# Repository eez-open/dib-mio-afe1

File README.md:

The [EEZ DIB](https://github.com/eez-open/modular-psu) 4-channel Hi-voltage/Hi-current AFE for [MIO168](https://github.com/eez-open/dib-mio168) module.

### Feature list
* [ADS131E04](https://www.ti.com/product/ADS131E04) 24-bit 4-channel simultaneous sampling ADC with SPI
* 5½ digit effective resolution
* 2 x Hi-voltage channels featuring software selectable 3 measurement ranges (±2.4 V, ±12 V, ±240 V), and one current range (±240 mA)
* 2 x Hi-current channels featuring software selectable 3 measurement ranes (±24 mA, ±1 A, ±10 A) and 2 voltage ranges (±2.4 V, ±12 V)
* Latching relays for lower continous power consumption
* On-board ±2.5 V low noise LDOs
* Optional Voltage reference (LTC6655-2.5)
* Active clamps on ADC inputs
* 20 x 5 mm fueses on hi-current channels (AIN3 and AIN4)
* Dimensions: 143 x 68.5 mm, 4-layer PCB

### r1B2 prototype

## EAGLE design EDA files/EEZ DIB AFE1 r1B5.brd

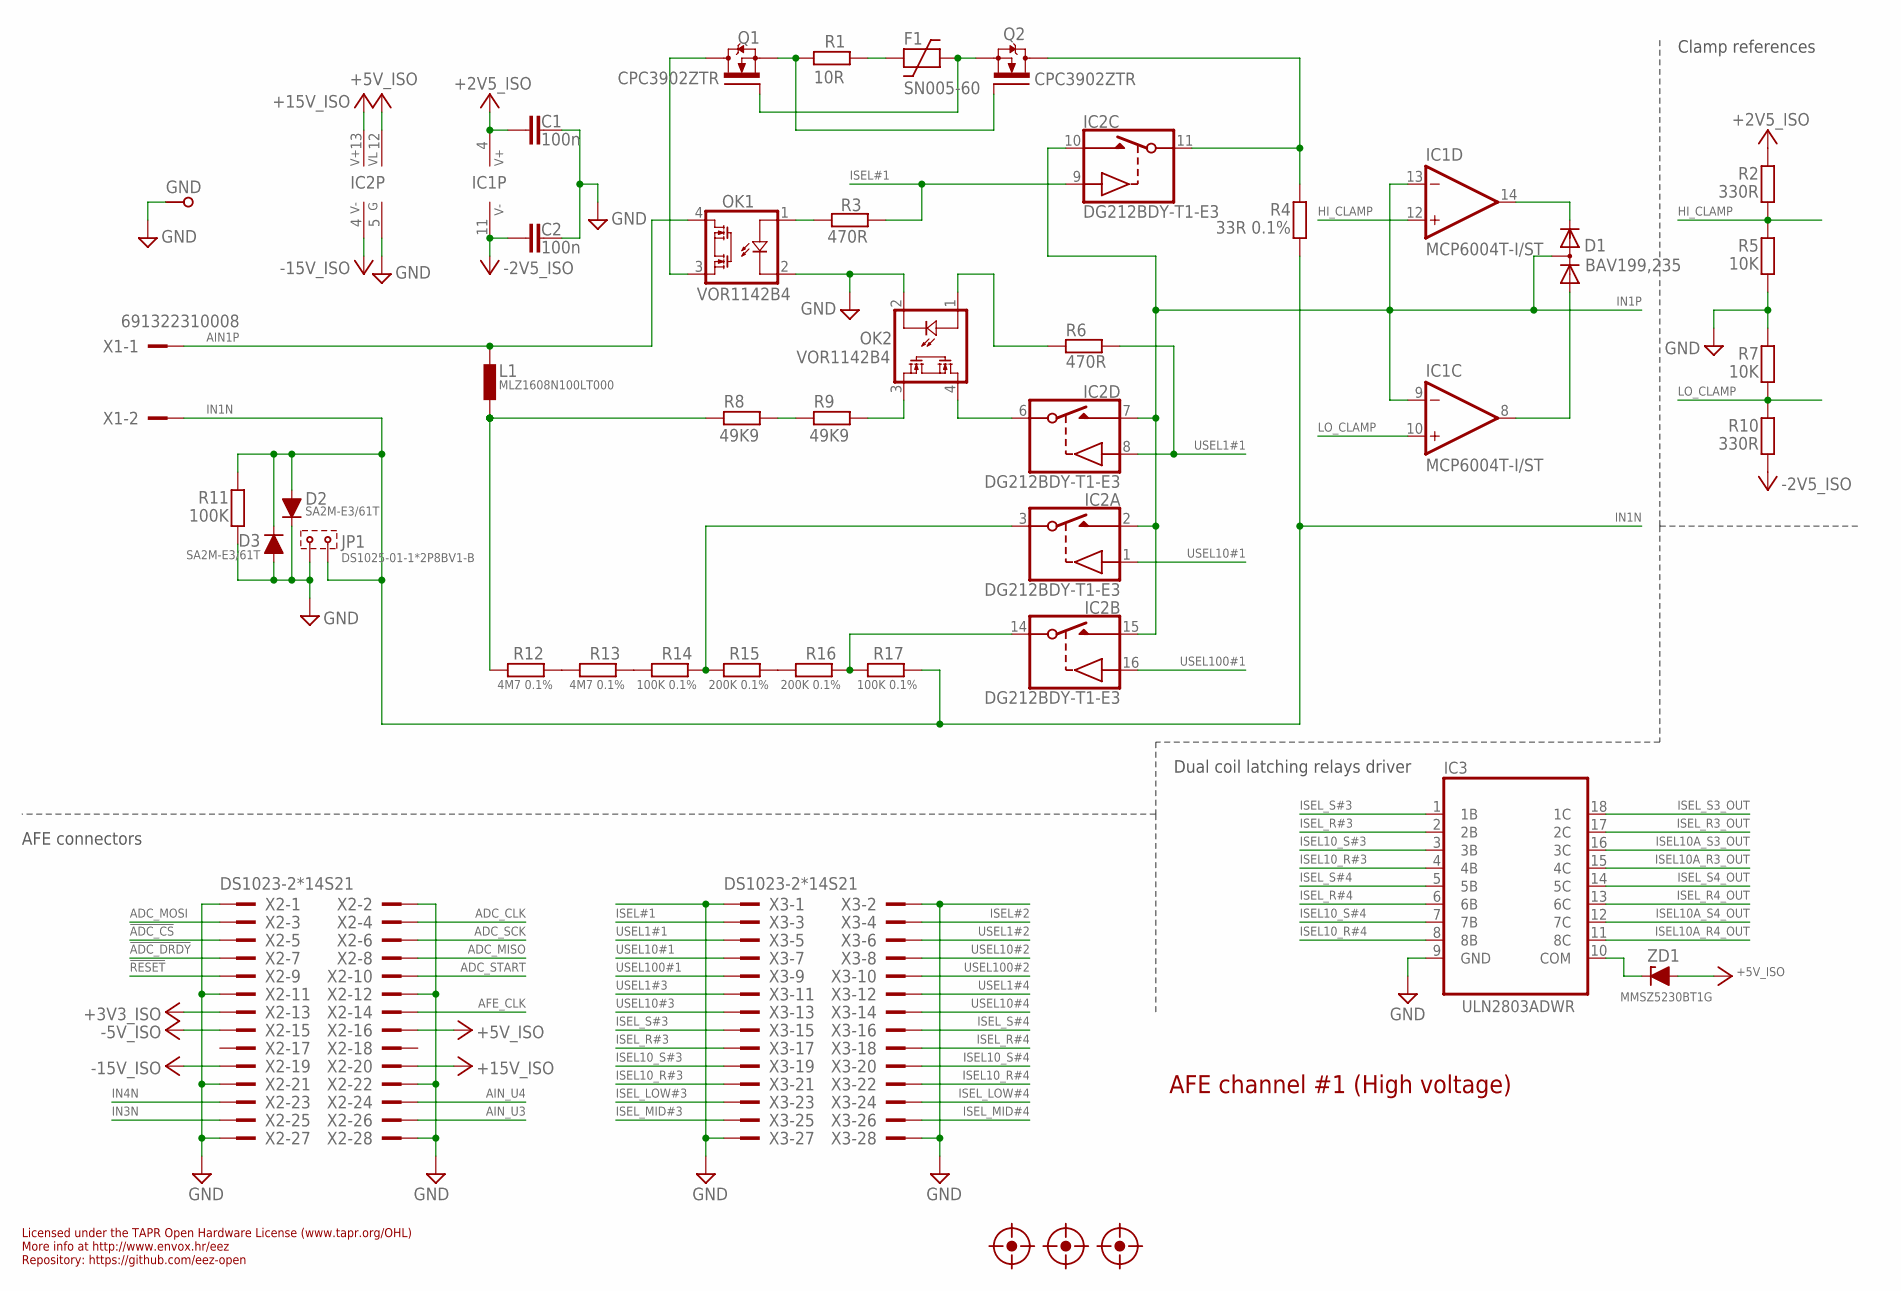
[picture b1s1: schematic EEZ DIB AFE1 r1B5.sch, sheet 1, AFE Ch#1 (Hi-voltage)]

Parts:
C1, C2: 100n; C0603
D1: BAV199,235; SOT23
D2, D3: SA2M-E3/61T; SMA_NARROW
F1: SN005-60; C1206-HV
FM1, FM2, FM3: FIDUCIAL_2; FIDUCIAL_DUAL
GND: PCB_TEST_TABSHIELD; PCB_SHIELD_TAB
IC1: MCP6004T-I/ST; PW(R-PDSO-G14)
IC2: DG212BDY-T1-E3; SO16
IC3: ULN2803ADWR; DW18_TEX-M
JP1: DS1025-01-1*2P8BV1-B; 2MM-2
L1: MLZ1608N100LT000; BEAD0603
OK1, OK2: VOR1142B4; DIL4-SMD
Q1, Q2: CPC3902ZTR; SOT230P700X180-4N
R1: 10R; R0805
R2, R10: 330R; R0805
R3, R6: 470R; R0805
R4: 33R 0.1%; R1206
R5, R7: 10K; R0805
R8, R9: 49K9; R1206
R11: 100K; R1206
R12, R13: 4M7 0.1%; R1206
R14, R17: 100K 0.1%; R1206
R15, R16: 200K 0.1%; R1206
X1: 691322310008
X2, X3: DS1023-2*14S21; TSW-114-07-F-D
ZD1: MMSZ5230BT1G; SOD123

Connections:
!ADC_CS: X2.5; also elsewhere on the board
!ADC_DRDY: X2.7; also elsewhere on the board
!RESET: X2.9; also elsewhere on the board
+2V5_ISO: C1.2, IC1.4 (V+), R2.1; also elsewhere on the board
+3V3_ISO: X2.13; also elsewhere on the board
+5V_ISO: IC2.12 (VL), X2.16, ZD1.A; also elsewhere on the board
+15V_ISO: IC2.13 (V+), X2.20; also elsewhere on the board
-2V5_ISO: C2.2, IC1.11 (V-), R10.2; also elsewhere on the board
-5V_ISO: X2.15; also elsewhere on the board
-15V_ISO: IC2.4 (V-), X2.19; also elsewhere on the board
ADC_CLK: X2.4; also elsewhere on the board
ADC_MISO: X2.8; also elsewhere on the board
ADC_MOSI: X2.3; also elsewhere on the board
ADC_SCK: X2.6; also elsewhere on the board
ADC_START: X2.10; also elsewhere on the board
AFE_CLK: X2.14
AIN1P: L1.P$2 (2), OK1.4 (S1), X1.1
AIN_U3: X2.26; also elsewhere on the board
AIN_U4: X2.24; also elsewhere on the board
CURR#1: IC2.11 (S), Q2.2 (D), Q2.4 (D), R4.2
CURR_IN#1: OK1.3 (S2), Q1.2 (D), Q1.4 (D)
GND: C1.1, C2.1, D2.1 (C), D3.2 (A), GND.1, IC2.5 (GND), IC3.9 (GND), JP1.2, OK1.2 (C), OK2.2 (C), R5.2, R7.1, R11.1, X2.1, X2.2, X2.11, X2.12, X2.21, X2.22, X2.27, X2.28, X3.1, X3.2, X3.27, X3.28; also elsewhere on the board
HI_CLAMP: IC1.12 (+IN), R2.2, R5.1; also elsewhere on the board
IN1N: D2.2 (A), D3.1 (C), JP1.1, R4.1, R11.2, R17.1, X1.2; also elsewhere on the board
IN1P: D1.3 (AC), IC1.9 (-IN), IC1.13 (-IN), IC2.2 (D), IC2.7 (D), IC2.10 (D), IC2.15 (D); also elsewhere on the board
IN3N: X2.25; also elsewhere on the board
IN4N: X2.23; also elsewhere on the board
ISEL10A_R3_OUT: IC3.15 (4C); also elsewhere on the board
ISEL10A_R4_OUT: IC3.11 (8C); also elsewhere on the board
ISEL10A_S3_OUT: IC3.16 (3C); also elsewhere on the board
ISEL10A_S4_OUT: IC3.12 (7C); also elsewhere on the board
ISEL10_R#3: IC3.4 (4B), X3.21
ISEL10_R#4: IC3.8 (8B), X3.22
ISEL10_S#3: IC3.3 (3B), X3.19
ISEL10_S#4: IC3.7 (7B), X3.20
ISEL#1: IC2.9 (IN), R3.2, X3.3
ISEL#2: X3.4; also elsewhere on the board
ISEL_LOW#3: X3.23; also elsewhere on the board
ISEL_LOW#4: X3.24; also elsewhere on the board
ISEL_MID#3: X3.25; also elsewhere on the board
ISEL_MID#4: X3.26; also elsewhere on the board
ISEL_R3_OUT: IC3.17 (2C); also elsewhere on the board
ISEL_R4_OUT: IC3.13 (6C); also elsewhere on the board
ISEL_R#3: IC3.2 (2B), X3.17
ISEL_R#4: IC3.6 (6B), X3.18
ISEL_S3_OUT: IC3.18 (1C); also elsewhere on the board
ISEL_S4_OUT: IC3.14 (5C); also elsewhere on the board
ISEL_S#3: IC3.1 (1B), X3.15
ISEL_S#4: IC3.5 (5B), X3.16
LO_CLAMP: IC1.10 (+IN), R7.2, R10.1; also elsewhere on the board
unnamed: L1.P$1 (1), R8.2, R12.2
unnamed: OK2.1 (A), R6.2
unnamed: F1.2, Q1.1 (G), Q2.3 (S)
unnamed: Q1.3 (S), Q2.1 (G), R1.2
unnamed: R15.1, R16.2
unnamed: IC3.10 (COM), ZD1.C
unnamed: OK1.1 (A), R3.1
unnamed: R13.1, R14.2
unnamed: R12.1, R13.2
unnamed: IC2.14 (S), R16.1, R17.2
unnamed: IC2.6 (S), OK2.4 (S1)
unnamed: OK2.3 (S2), R9.1
unnamed: F1.1, R1.1
unnamed: D1.2 (C), IC1.14 (OUT)
unnamed: D1.1 (A), IC1.8 (OUT)
unnamed: R8.1, R9.2
unnamed: IC2.3 (S), R14.1, R15.2
USEL1#1: IC2.8 (IN), R6.1, X3.5
USEL1#2: X3.6; also elsewhere on the board
USEL1#3: X3.11; also elsewhere on the board
USEL1#4: X3.12; also elsewhere on the board
USEL10#1: IC2.1 (IN), X3.7
USEL10#2: X3.8; also elsewhere on the board
USEL10#3: X3.13; also elsewhere on the board
USEL10#4: X3.14; also elsewhere on the board
USEL100#1: IC2.16 (IN), X3.9
USEL100#2: X3.10; also elsewhere on the board

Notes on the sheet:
Licensed under the TAPR Open Hardware License (www.tapr.org/OHL)
Repository: https://github.com/eez-open
More info at http://www.envox.hr/eez
AFE channel #1 (High voltage)
Dual coil latching relays driver
AFE connectors
Clamp references

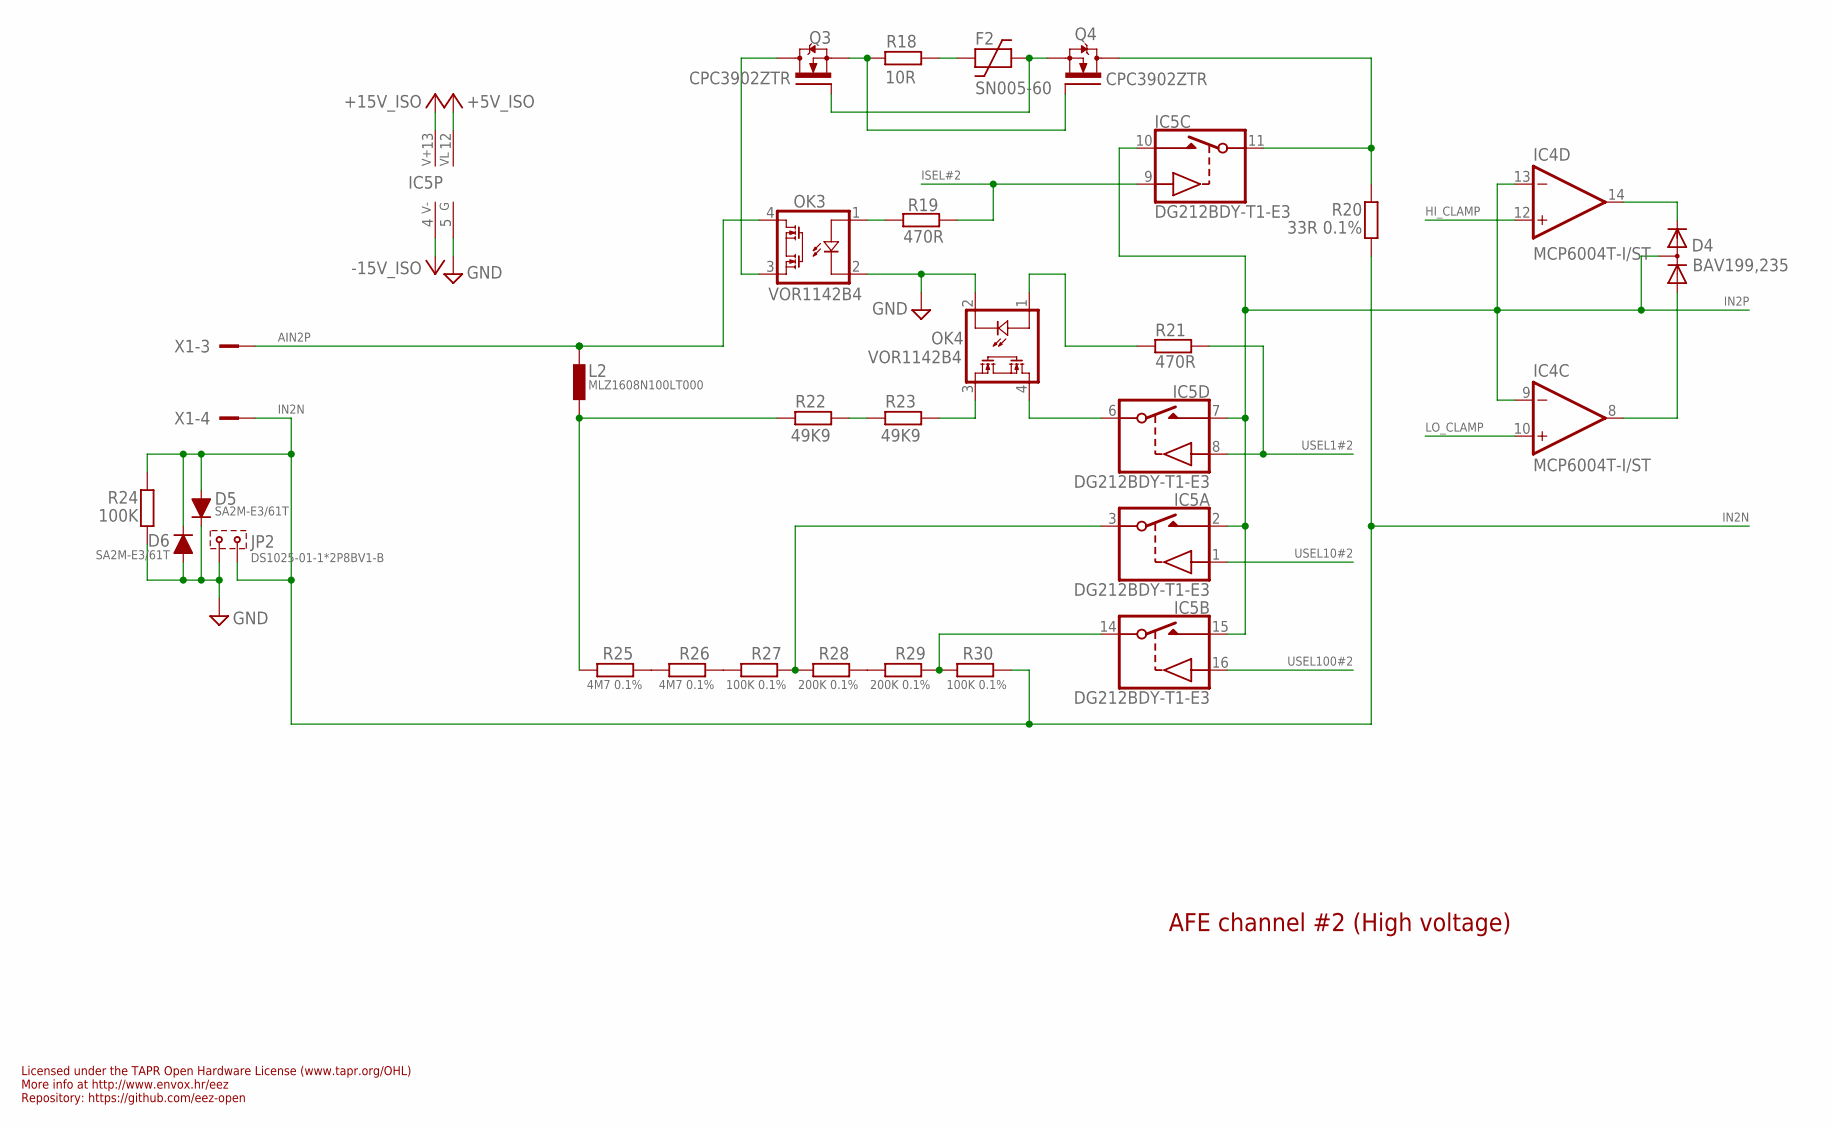
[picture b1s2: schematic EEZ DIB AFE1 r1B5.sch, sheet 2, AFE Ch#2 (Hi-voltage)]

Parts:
D4: BAV199,235; SOT23
D5, D6: SA2M-E3/61T; SMA_NARROW
F2: SN005-60; C1206-HV
IC4: MCP6004T-I/ST; PW(R-PDSO-G14)
IC5: DG212BDY-T1-E3; SO16
JP2: DS1025-01-1*2P8BV1-B; 2MM-2
L2: MLZ1608N100LT000; BEAD0603
OK3, OK4: VOR1142B4; DIL4-SMD
Q3, Q4: CPC3902ZTR; SOT230P700X180-4N
R18: 10R; R0805
R19, R21: 470R; R0805
R20: 33R 0.1%; R1206
R22, R23: 49K9; R1206
R24: 100K; R1206
R25, R26: 4M7 0.1%; R1206
R27, R30: 100K 0.1%; R1206
R28, R29: 200K 0.1%; R1206
X1: 691322310008

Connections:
+5V_ISO: IC5.12 (VL); also elsewhere on the board
+15V_ISO: IC5.13 (V+); also elsewhere on the board
-15V_ISO: IC5.4 (V-); also elsewhere on the board
AIN2P: L2.P$2 (2), OK3.4 (S1), X1.3
CURR#2: IC5.11 (S), Q4.2 (D), Q4.4 (D), R20.2
CURR_IN#2: OK3.3 (S2), Q3.2 (D), Q3.4 (D)
GND: D5.1 (C), D6.2 (A), IC5.5 (GND), JP2.2, OK3.2 (C), OK4.2 (C), R24.1; also elsewhere on the board
HI_CLAMP: IC4.12 (+IN); also elsewhere on the board
IN2N: D5.2 (A), D6.1 (C), JP2.1, R20.1, R24.2, R30.1, X1.4; also elsewhere on the board
IN2P: D4.3 (AC), IC4.9 (-IN), IC4.13 (-IN), IC5.2 (D), IC5.7 (D), IC5.10 (D), IC5.15 (D); also elsewhere on the board
ISEL#2: IC5.9 (IN), R19.2; also elsewhere on the board
LO_CLAMP: IC4.10 (+IN); also elsewhere on the board
unnamed: L2.P$1 (1), R22.2, R25.2
unnamed: IC5.14 (S), R29.1, R30.2
unnamed: IC5.6 (S), OK4.4 (S1)
unnamed: OK4.3 (S2), R23.1
unnamed: D4.2 (C), IC4.14 (OUT)
unnamed: D4.1 (A), IC4.8 (OUT)
unnamed: R22.1, R23.2
unnamed: IC5.3 (S), R27.1, R28.2
unnamed: R28.1, R29.2
unnamed: R26.1, R27.2
unnamed: R25.1, R26.2
unnamed: OK3.1 (A), R19.1
unnamed: OK4.1 (A), R21.2
unnamed: F2.2, Q3.1 (G), Q4.3 (S)
unnamed: Q3.3 (S), Q4.1 (G), R18.2
unnamed: F2.1, R18.1
USEL1#2: IC5.8 (IN), R21.1; also elsewhere on the board
USEL10#2: IC5.1 (IN); also elsewhere on the board
USEL100#2: IC5.16 (IN); also elsewhere on the board

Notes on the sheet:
Licensed under the TAPR Open Hardware License (www.tapr.org/OHL)
Repository: https://github.com/eez-open
More info at http://www.envox.hr/eez
AFE channel #2 (High voltage)

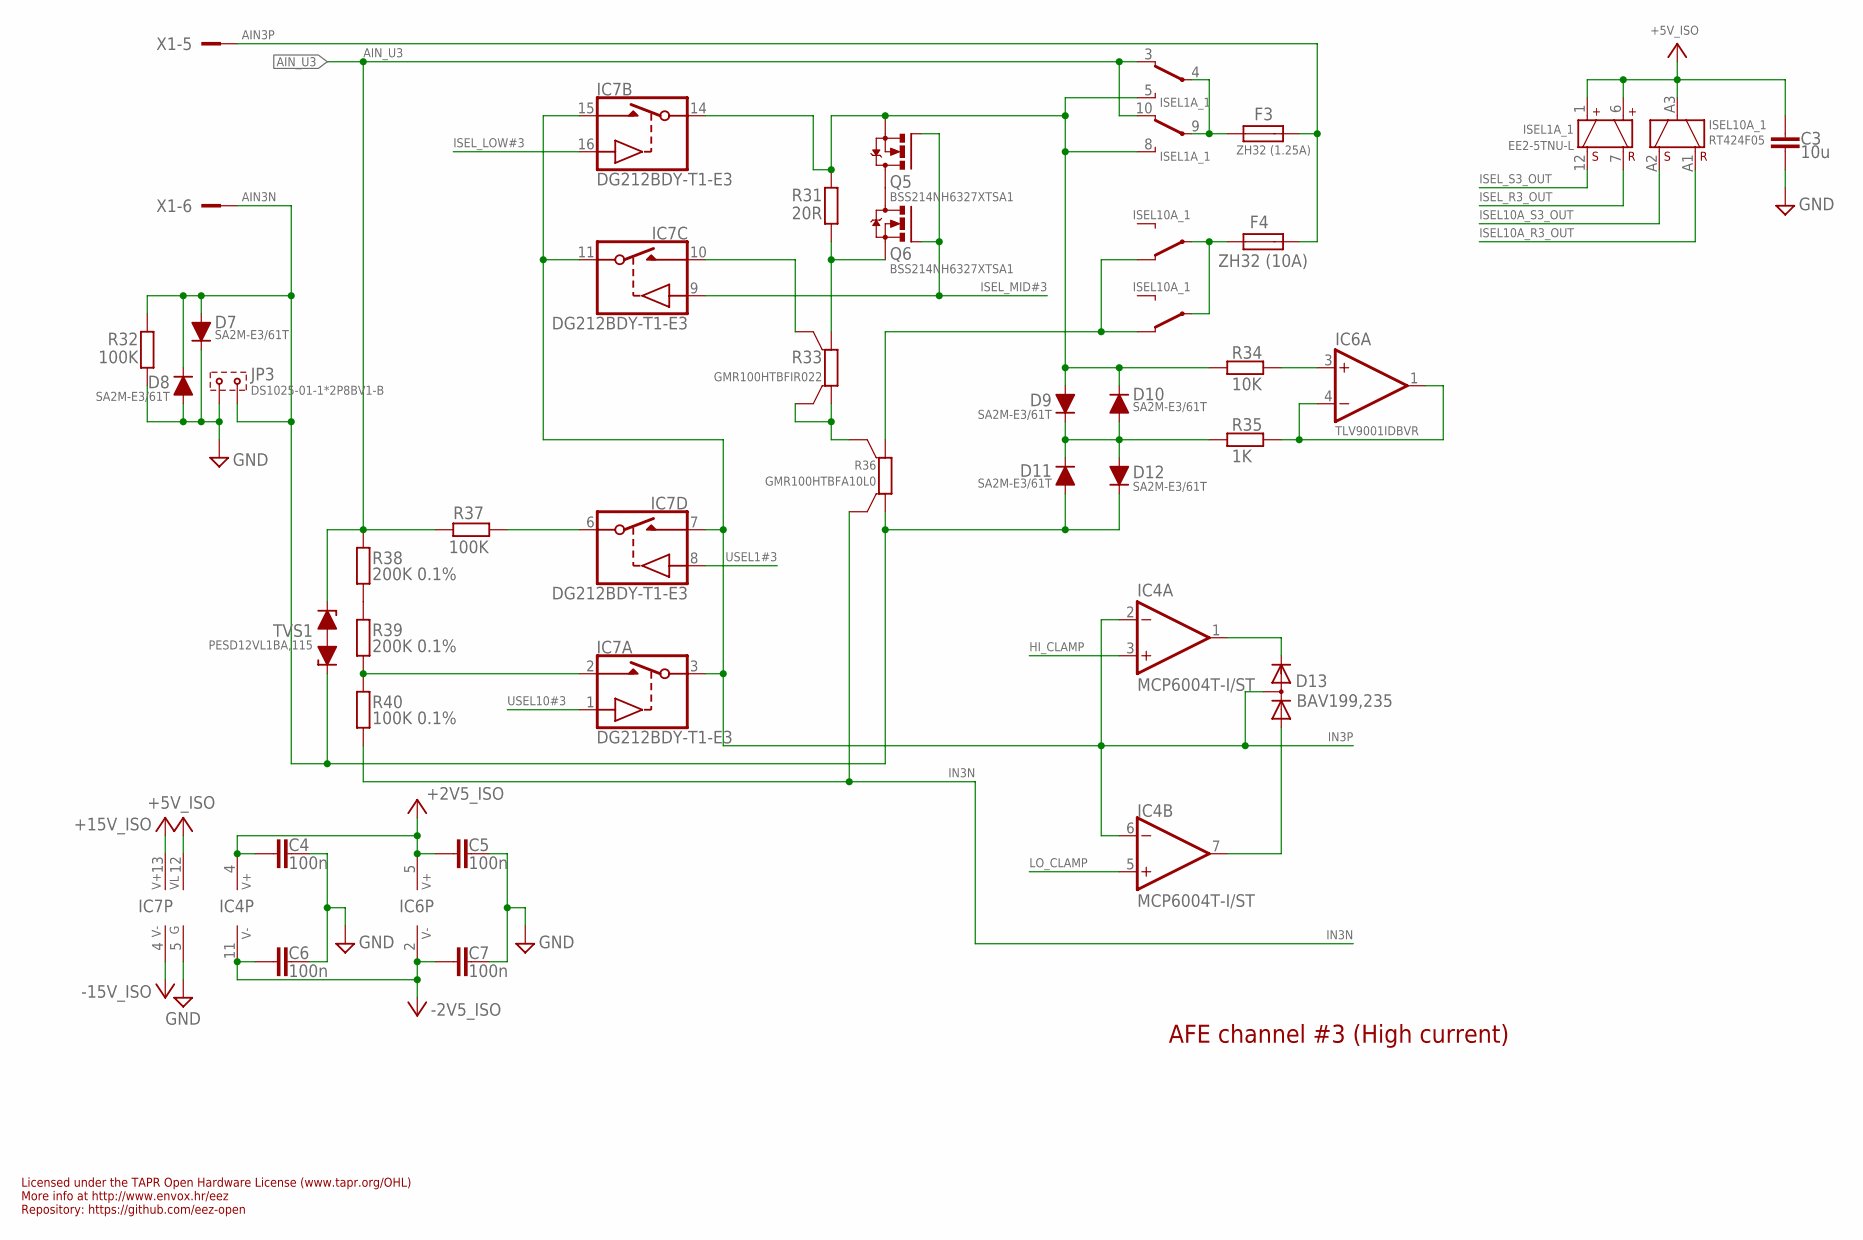
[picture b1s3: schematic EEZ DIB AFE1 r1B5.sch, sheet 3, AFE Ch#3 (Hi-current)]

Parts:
C3: 10u; C1206
C4, C5, C6, C7: 100n; C0603
D7, D8, D9, D10, D11, D12: SA2M-E3/61T; SMA_NARROW
D13: BAV199,235; SOT23
F3: ZH32 (1.25A); ZH32
F4: ZH32 (10A); ZH32
IC4: MCP6004T-I/ST; PW(R-PDSO-G14)
IC6: TLV9001IDBVR; DBV5
IC7: DG212BDY-T1-E3; SO16
ISEL1A_1: EE2-5TNU-L; G6SK-2F
ISEL10A_1: RT424F05; RT424FXX
JP3: DS1025-01-1*2P8BV1-B; 2MM-2
Q5: BSS214NH6327XTSA1; SOT103P240X110-3N; MPN 2N7002-7-F
Q6: BSS214NH6327XTSA1; SOT103P240X110-3N
R31: 20R; R1206
R32, R37: 100K; R1206
R33: GMR100HTBFIR022; R_2512-4WIRE
R34: 10K; R0805
R35: 1K; R0805
R36: GMR100HTBFA10L0; R_2512-4WIRE
R38, R39: 200K 0.1%; R1206
R40: 100K 0.1%; R1206
TVS1: PESD12VL1BA,115; SOD323-BIDIR
X1: 691322310008

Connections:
+2V5_ISO: C4.2, C5.2, IC4.4 (V+), IC6.5 (V+); also elsewhere on the board
+5V_ISO: C3.1, IC7.12 (VL), ISEL1A_1.1 (S+), ISEL1A_1.6 (R+), ISEL10A_1.A3 (COM); also elsewhere on the board
+15V_ISO: IC7.13 (V+); also elsewhere on the board
-2V5_ISO: C6.2, C7.2, IC4.11 (V-), IC6.2 (V-); also elsewhere on the board
-15V_ISO: IC7.4 (V-); also elsewhere on the board
AIN3N: D7.2 (A), D8.1 (C), D11.2 (A), D12.1 (C), JP3.1, R32.2, R36.1, TVS1.C1 (1), X1.6
AIN3P: F3.2, F4.2, X1.5
AIN3P_FUSED: F3.1, ISEL1A_1.4 (COM), ISEL1A_1.9 (COM)
AIN_U3: ISEL1A_1.3 (NC), ISEL1A_1.10 (NC), R37.2, R38.2, TVS1.C2 (2); also elsewhere on the board
GND: C3.2, C4.1, C5.1, C6.1, C7.1, D7.1 (C), D8.2 (A), IC7.5 (GND), JP3.2, R32.1; also elsewhere on the board
HI_CLAMP: IC4.3 (+IN); also elsewhere on the board
HI_CURR#2: ISEL10A_1.12 (NC), ISEL10A_1.22 (NC), R36.2
IN3N: R36.1S, R40.1; also elsewhere on the board
IN3P: D13.3 (AC), IC4.2 (-IN), IC4.6 (-IN), IC7.3 (S), IC7.7 (D), IC7.11 (S), IC7.15 (D); also elsewhere on the board
ISEL10A_R3_OUT: ISEL10A_1.A1 (R); also elsewhere on the board
ISEL10A_S3_OUT: ISEL10A_1.A2 (S); also elsewhere on the board
ISEL_LOW#3: IC7.16 (IN); also elsewhere on the board
ISEL_MID#3: IC7.9 (IN), Q5.1 (G), Q6.1 (G); also elsewhere on the board
ISEL_R3_OUT: ISEL1A_1.7 (R-); also elsewhere on the board
ISEL_S3_OUT: ISEL1A_1.12 (S-); also elsewhere on the board
LO_CLAMP: IC4.5 (+IN); also elsewhere on the board
unnamed: F4.1, ISEL10A_1.11 (COM), ISEL10A_1.21 (COM)
unnamed: R33.1, R33.1S, R36.2S
unnamed: Q6.2 (S), R31.1, R33.2
unnamed: Q5.3 (D), Q6.3 (D)
unnamed: IC7.10 (D), R33.2S
unnamed: D9.1 (C), D10.2 (A), D11.1 (C), D12.2 (A), R35.2
unnamed: D9.2 (A), D10.1 (C), IC7.14 (S), ISEL1A_1.5 (NO), ISEL1A_1.8 (NO), Q5.2 (S), R31.2, R34.2
unnamed: IC6.1 (OUT), IC6.4 (-IN), R35.1
unnamed: IC6.3 (+IN), R34.1
unnamed: R38.1, R39.2
unnamed: IC7.2 (D), R39.1, R40.2
unnamed: IC7.6 (S), R37.1
unnamed: D13.2 (C), IC4.1 (OUT)
unnamed: D13.1 (A), IC4.7 (OUT)
USEL1#3: IC7.8 (IN); also elsewhere on the board
USEL10#3: IC7.1 (IN); also elsewhere on the board

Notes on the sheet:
Licensed under the TAPR Open Hardware License (www.tapr.org/OHL)
Repository: https://github.com/eez-open
More info at http://www.envox.hr/eez
AFE channel #3 (High current)

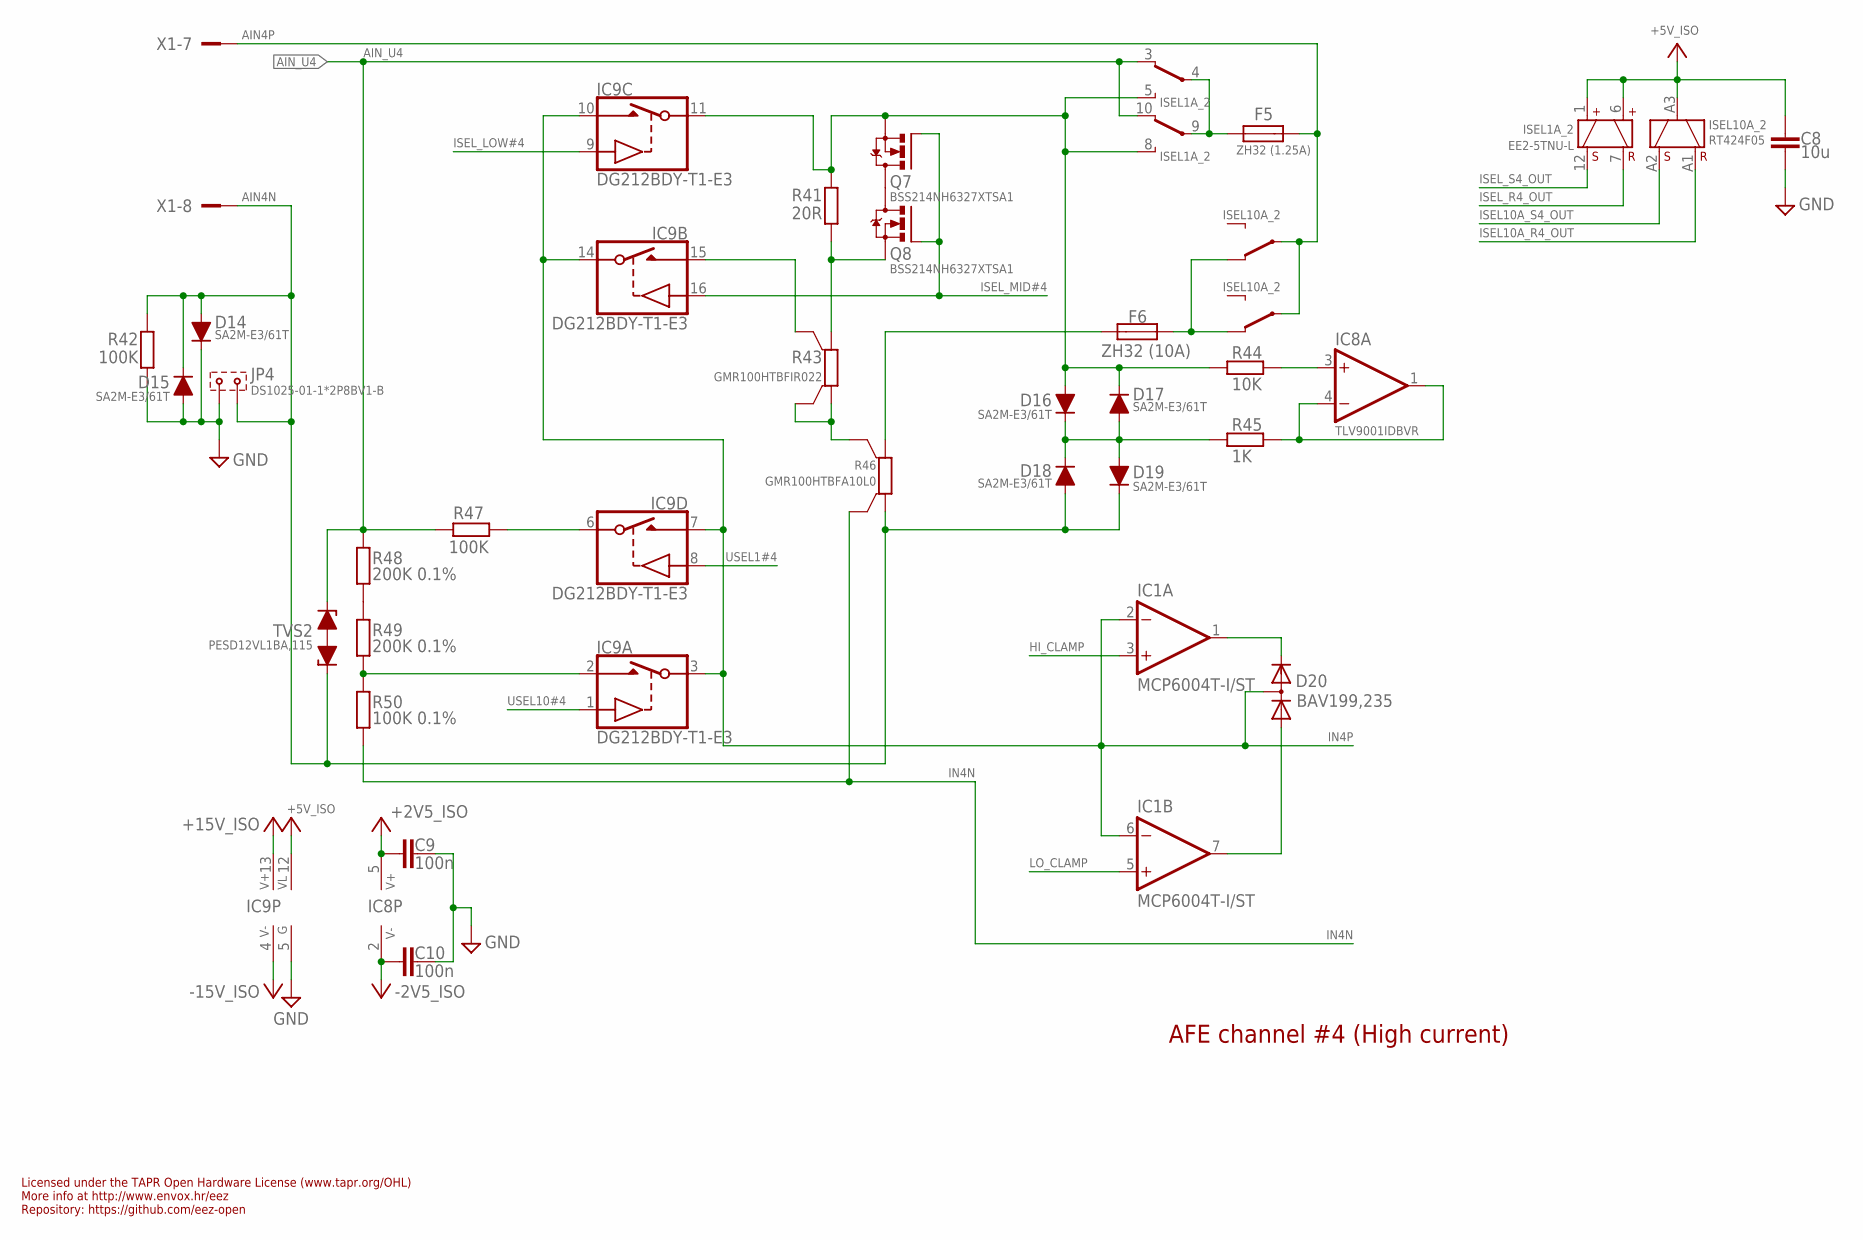
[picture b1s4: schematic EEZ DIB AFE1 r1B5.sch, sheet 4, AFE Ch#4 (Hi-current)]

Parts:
C8: 10u; C1206
C9, C10: 100n; C0603
D14, D15, D16, D17, D18, D19: SA2M-E3/61T; SMA_NARROW
D20: BAV199,235; SOT23
F5: ZH32 (1.25A); ZH32
F6: ZH32 (10A); ZH32
IC1: MCP6004T-I/ST; PW(R-PDSO-G14)
IC8: TLV9001IDBVR; DBV5
IC9: DG212BDY-T1-E3; SO16
ISEL1A_2: EE2-5TNU-L; G6SK-2F
ISEL10A_2: RT424F05; RT424FXX
JP4: DS1025-01-1*2P8BV1-B; 2MM-2
Q7: BSS214NH6327XTSA1; SOT103P240X110-3N; MPN 2N7002-7-F
Q8: BSS214NH6327XTSA1; SOT103P240X110-3N
R41: 20R; R1206
R42, R47: 100K; R1206
R43: GMR100HTBFIR022; R_2512-4WIRE
R44: 10K; R0805
R45: 1K; R0805
R46: GMR100HTBFA10L0; R_2512-4WIRE
R48, R49: 200K 0.1%; R1206
R50: 100K 0.1%; R1206
TVS2: PESD12VL1BA,115; SOD323-BIDIR
X1: 691322310008

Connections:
+2V5_ISO: C9.2, IC8.5 (V+); also elsewhere on the board
+5V_ISO: C8.1, IC9.12 (VL), ISEL1A_2.1 (S+), ISEL1A_2.6 (R+), ISEL10A_2.A3 (COM); also elsewhere on the board
+15V_ISO: IC9.13 (V+); also elsewhere on the board
-2V5_ISO: C10.2, IC8.2 (V-); also elsewhere on the board
-15V_ISO: IC9.4 (V-); also elsewhere on the board
AIN4N: D14.2 (A), D15.1 (C), D18.2 (A), D19.1 (C), JP4.1, R42.2, R46.1, TVS2.C1 (1), X1.8
AIN4P: F5.2, ISEL10A_2.11 (COM), ISEL10A_2.21 (COM), X1.7
AIN4P_FUSED: F5.1, ISEL1A_2.4 (COM), ISEL1A_2.9 (COM)
AIN_U4: ISEL1A_2.3 (NC), ISEL1A_2.10 (NC), R47.2, R48.2, TVS2.C2 (2); also elsewhere on the board
GND: C8.2, C9.1, C10.1, D14.1 (C), D15.2 (A), IC9.5 (GND), JP4.2, R42.1; also elsewhere on the board
HI_CLAMP: IC1.3 (+IN); also elsewhere on the board
HI_CURR#4: F6.2, R46.2
IN4N: R46.1S, R50.1; also elsewhere on the board
IN4P: D20.3 (AC), IC1.2 (-IN), IC1.6 (-IN), IC9.3 (S), IC9.7 (D), IC9.10 (D), IC9.14 (S); also elsewhere on the board
ISEL10A_R4_OUT: ISEL10A_2.A1 (R); also elsewhere on the board
ISEL10A_S4_OUT: ISEL10A_2.A2 (S); also elsewhere on the board
ISEL_LOW#4: IC9.9 (IN); also elsewhere on the board
ISEL_MID#4: IC9.16 (IN), Q7.1 (G), Q8.1 (G); also elsewhere on the board
ISEL_R4_OUT: ISEL1A_2.7 (R-); also elsewhere on the board
ISEL_S4_OUT: ISEL1A_2.12 (S-); also elsewhere on the board
LO_CLAMP: IC1.5 (+IN); also elsewhere on the board
unnamed: F6.1, ISEL10A_2.12 (NC), ISEL10A_2.22 (NC)
unnamed: Q8.2 (S), R41.1, R43.2
unnamed: D16.1 (C), D17.2 (A), D18.1 (C), D19.2 (A), R45.2
unnamed: D16.2 (A), D17.1 (C), IC9.11 (S), ISEL1A_2.5 (NO), ISEL1A_2.8 (NO), Q7.2 (S), R41.2, R44.2
unnamed: IC8.1 (OUT), IC8.4 (-IN), R45.1
unnamed: IC8.3 (+IN), R44.1
unnamed: R48.1, R49.2
unnamed: IC9.2 (D), R49.1, R50.2
unnamed: IC9.6 (S), R47.1
unnamed: D20.2 (C), IC1.1 (OUT)
unnamed: D20.1 (A), IC1.7 (OUT)
unnamed: IC9.15 (D), R43.2S
unnamed: Q7.3 (D), Q8.3 (D)
unnamed: R43.1, R43.1S, R46.2S
USEL1#4: IC9.8 (IN); also elsewhere on the board
USEL10#4: IC9.1 (IN); also elsewhere on the board

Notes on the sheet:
Licensed under the TAPR Open Hardware License (www.tapr.org/OHL)
Repository: https://github.com/eez-open
More info at http://www.envox.hr/eez
AFE channel #4 (High current)

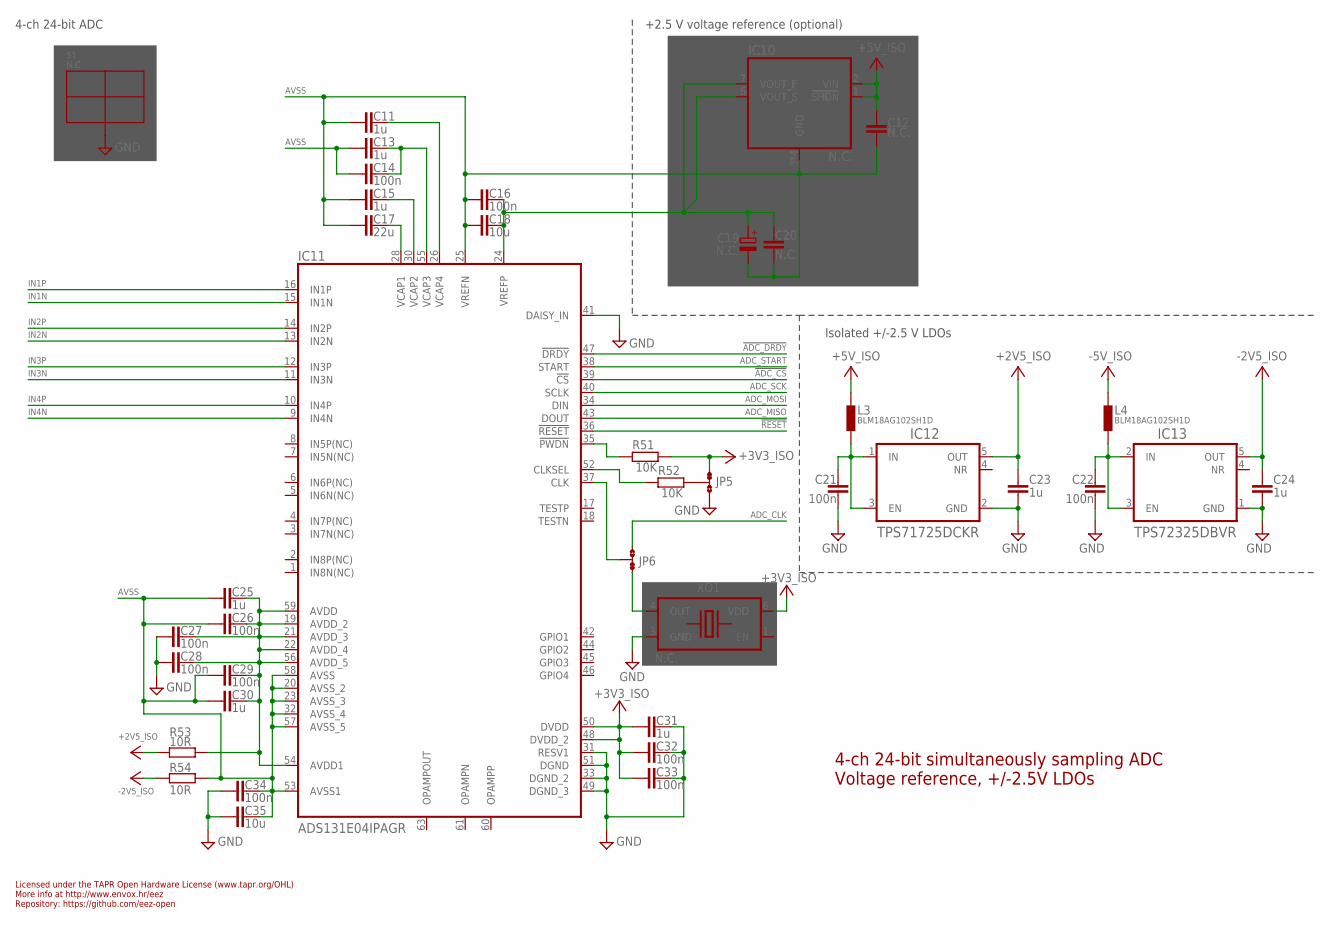
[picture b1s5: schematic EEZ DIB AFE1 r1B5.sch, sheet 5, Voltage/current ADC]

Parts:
C11, C13, C15, C23, C24, C25, C30, C31: 1u; C0805
C12: N.C.; C1206
C14, C16, C21, C22, C26, C27, C28, C29, C32, C33, C34: 100n; C0603
C17: 22u; C1206
C18, C35: 10u; C1206
C19: N.C.; EC1206
C20: N.C.; C050-075X110
IC10: N.C.; MSOP-8_MS_LIT
IC11: ADS131E04IPAGR; PAG64
IC12: TPS71725DCKR; DCK5
IC13: TPS72325DBVR; DBV5
JP5, JP6: JP3-CUT-0805-ROTATED; JP3-0805-CUT2
L3, L4: BLM18AG102SH1D; BEAD0603
R51, R52: 10K; R0805
R53, R54: 10R; R0805
S1: N.C.; 2118732-2
XO1: N.C.; XLH

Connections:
!ADC_CS: IC11.39 (!CS); also elsewhere on the board
!ADC_DRDY: IC11.47 (!DRDY); also elsewhere on the board
!RESET: IC11.36 (!RESET); also elsewhere on the board
+2V5_ADC: C25.2, C26.1, C27.1, C28.1, C29.1, C30.2, IC11.19 (AVDD_2), IC11.21 (AVDD_3), IC11.22 (AVDD_4), IC11.54 (AVDD1), IC11.56 (AVDD_5), IC11.59 (AVDD), R53.2
+2V5_ISO: C23.2, IC12.5 (OUT), R53.1; also elsewhere on the board
+3V3_ISO: C31.1, C32.2, C33.2, IC11.48 (DVDD_2), IC11.50 (DVDD), JP5.NC, R51.2, XO1.6 (VDD); also elsewhere on the board
+5V_ISO: C12.1, IC10.1 (!SHDN), IC10.2 (VIN), L3.P$2 (2); also elsewhere on the board
-2V5_ISO: C24.2, IC13.5 (OUT), R54.2; also elsewhere on the board
-5V_ISO: L4.P$2 (2); also elsewhere on the board
ADC_CLK: JP6.NO; also elsewhere on the board
ADC_MISO: IC11.43 (DOUT); also elsewhere on the board
ADC_MOSI: IC11.34 (DIN); also elsewhere on the board
ADC_SCK: IC11.40 (SCLK); also elsewhere on the board
ADC_START: IC11.38 (START); also elsewhere on the board
AVSS: C11.1, C12.2, C13.1, C14.2, C15.1, C16.2, C17.1, C18.2, C19.-, C20.2, C25.1, C26.2, C29.2, C30.1, C34.1, C35.1, IC10.3 (GND), IC10.4 (GND), IC10.5 (GND), IC10.8 (GND), IC11.20 (AVSS_2), IC11.23 (AVSS_3), IC11.25 (VREFN), IC11.32 (AVSS_4), IC11.53 (AVSS1), IC11.57 (AVSS_5), IC11.58 (AVSS), R54.1
GND: C21.2, C22.2, C23.1, C24.1, C27.2, C28.2, C31.2, C32.1, C33.1, C34.2, C35.2, IC11.31 (RESV1), IC11.33 (DGND_2), IC11.41 (DAISY_IN), IC11.49 (DGND_3), IC11.51 (DGND), IC12.2 (GND), IC13.1 (GND), JP5.NO, S1.SH.1, S1.SH.2, S1.SH.3, S1.SH.4, S1.SH.5, S1.SH.6, S1.SH.7, S1.SH.8, XO1.3 (GND); also elsewhere on the board
IN1N: IC11.15 (IN1N); also elsewhere on the board
IN1P: IC11.16 (IN1P); also elsewhere on the board
IN2N: IC11.13 (IN2N); also elsewhere on the board
IN2P: IC11.14 (IN2P); also elsewhere on the board
IN3N: IC11.11 (IN3N); also elsewhere on the board
IN3P: IC11.12 (IN3P); also elsewhere on the board
IN4N: IC11.9 (IN4N); also elsewhere on the board
IN4P: IC11.10 (IN4P); also elsewhere on the board
unnamed: IC11.52 (CLKSEL), R52.1
unnamed: C21.1, IC12.1 (IN), IC12.3 (EN), L3.P$1 (1)
unnamed: C22.1, IC13.2 (IN), IC13.3 (EN), L4.P$1 (1)
unnamed: JP5.COM, R52.2
unnamed: C17.2, IC11.28 (VCAP1)
unnamed: C15.2, IC11.30 (VCAP2)
unnamed: C13.2, C14.1, IC11.55 (VCAP3)
unnamed: C11.2, IC11.26 (VCAP4)
unnamed: IC11.37 (CLK), JP6.COM
unnamed: JP6.NC, XO1.4 (OUT)
unnamed: IC11.35 (!PWDN), R51.1
VREFP: C16.1, C18.1, C19.+, C20.1, IC10.6 (VOUT_S), IC10.7 (VOUT_F), IC11.24 (VREFP)

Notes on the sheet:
Licensed under the TAPR Open Hardware License (www.tapr.org/OHL)
Repository: https://github.com/eez-open
More info at http://www.envox.hr/eez
4-ch 24-bit simultaneously sampling ADC Voltage reference, +/-2.5V LDOs
4-ch 24-bit ADC
+2.5 V voltage reference (optional)
Isolated +/-2.5 V LDOs

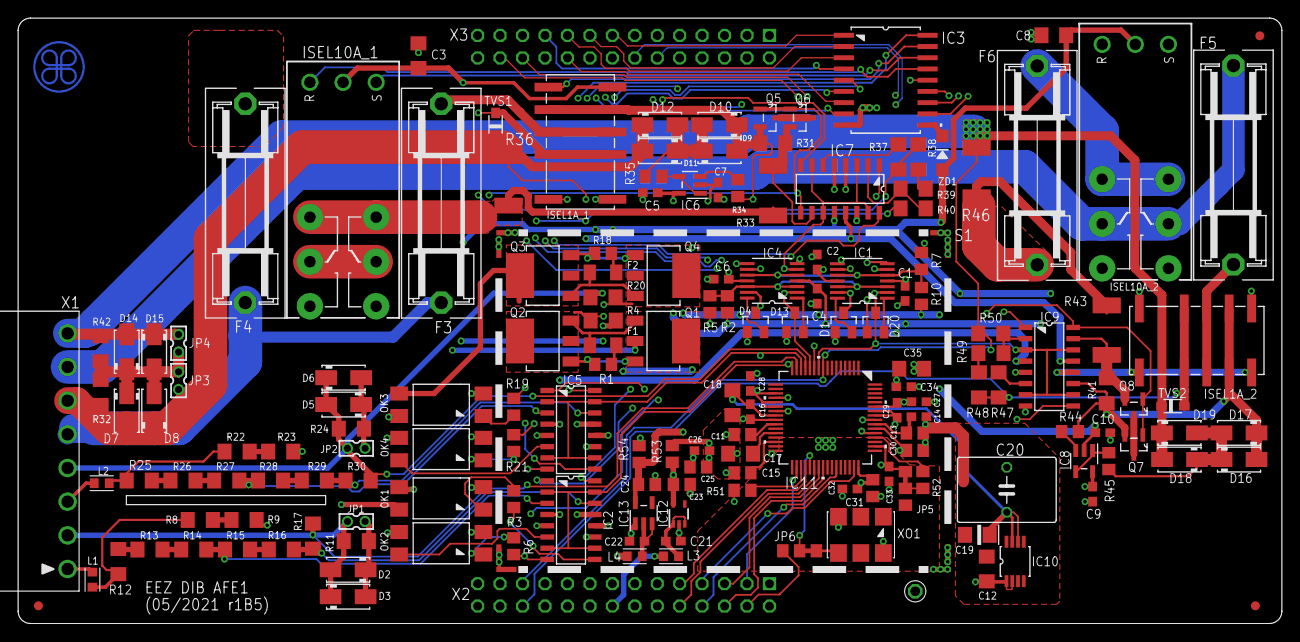
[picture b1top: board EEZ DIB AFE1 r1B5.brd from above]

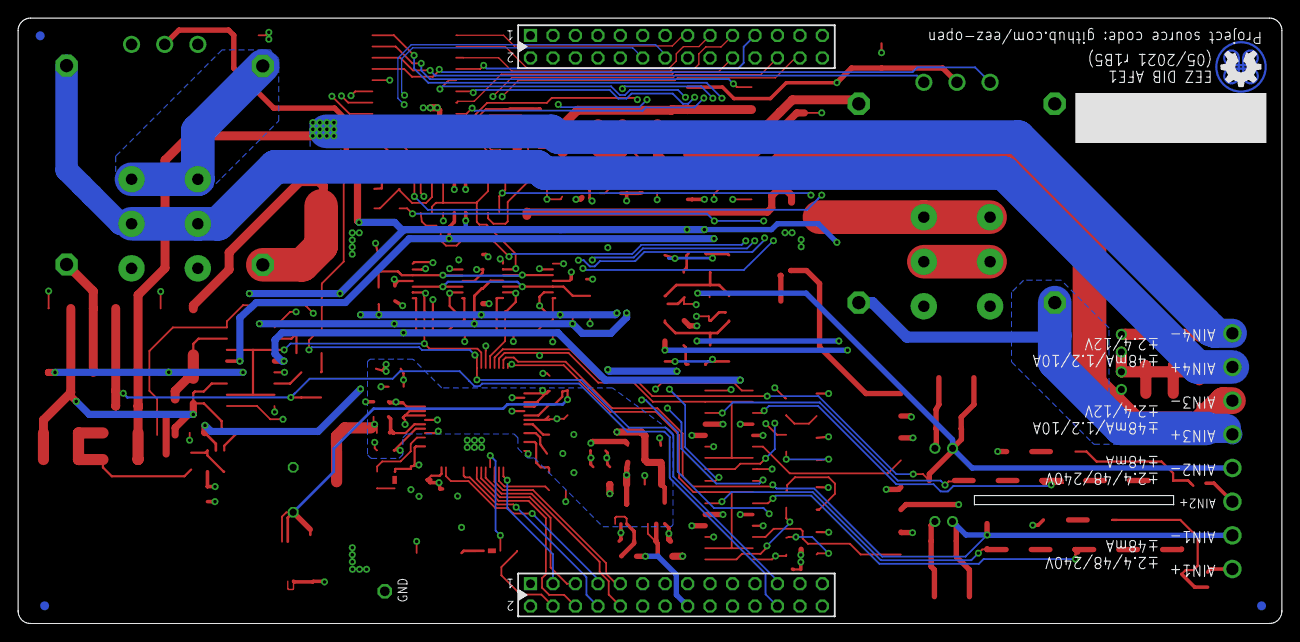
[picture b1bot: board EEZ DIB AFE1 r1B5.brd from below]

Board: 4 copper layers, 143.0 x 68.5 mm, 167 parts (2 on the bottom side), 149 nets.

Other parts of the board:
EEZ_SIGNATURE: SIGNATURESMALL; SIGNATURE_5MM

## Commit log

2021-01-23 small PCB layout changes
2021-01-24 PCB silkscreen fix
2021-01-25 image filenames fixed
2021-01-27 readme.md image link
2021-01-27 active clamp op-amps changed
2021-05-09 #1, #2, BOM (r1B5)
2021-05-14 New Rsense values, PCB layout adjustment for mid range Rsense
2021-05-14 BOM update

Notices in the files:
parts and their libraries:
EEZ_DIB: This work is licensed under the TAPR Open Hardware License.
